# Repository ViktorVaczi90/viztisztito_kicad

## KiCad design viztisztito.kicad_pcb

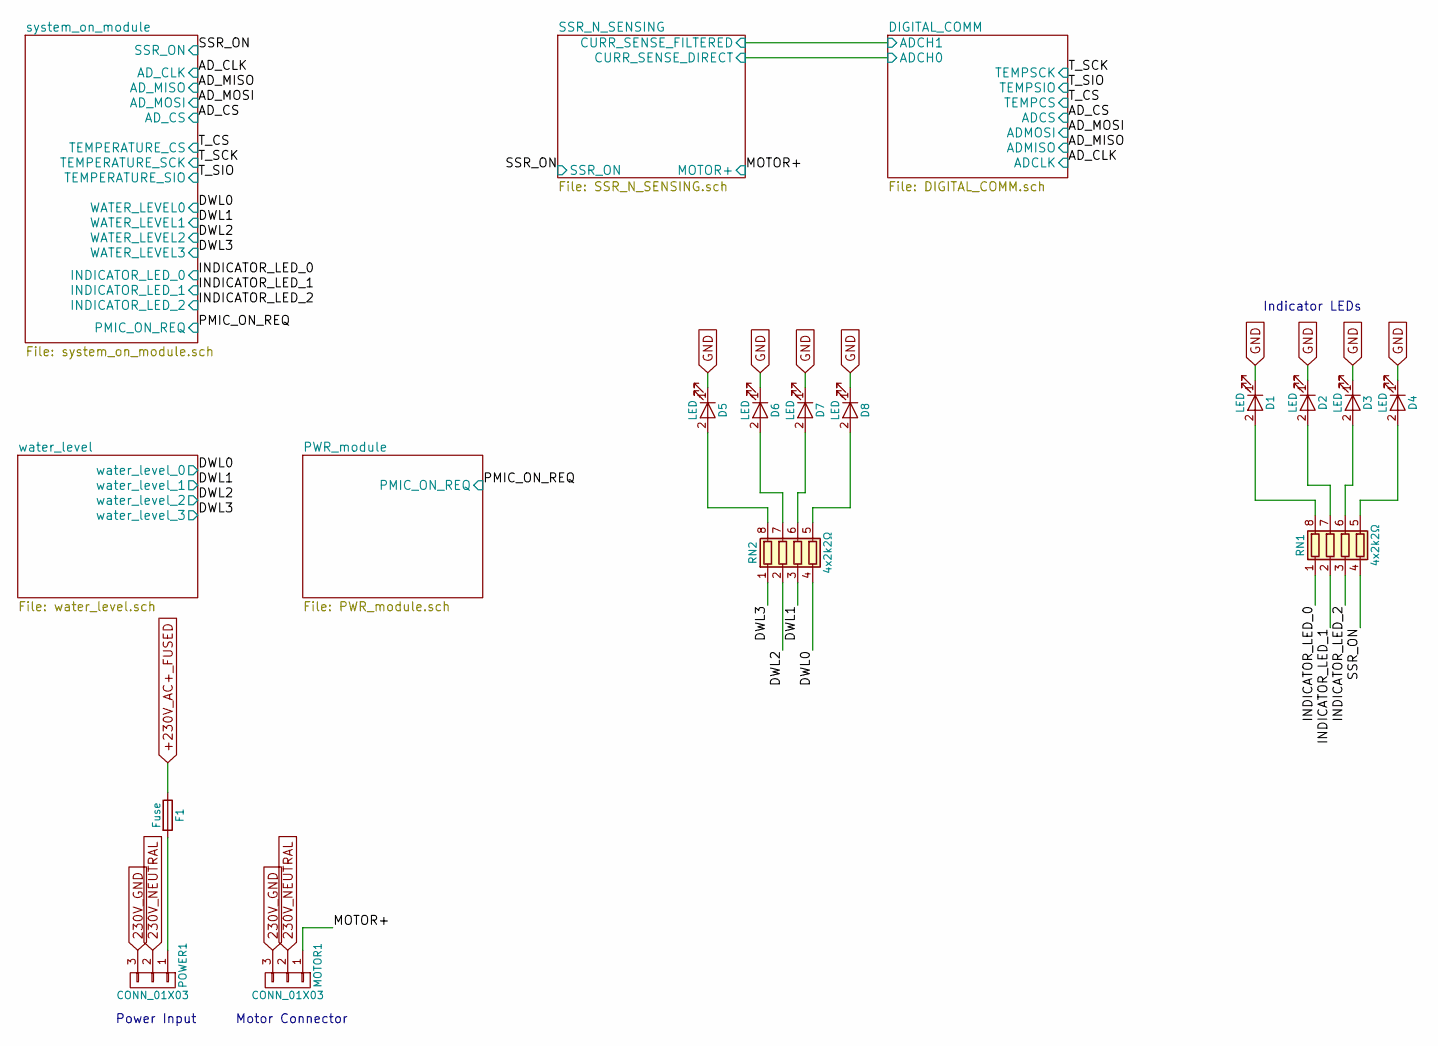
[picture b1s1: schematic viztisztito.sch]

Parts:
D1, D2, D3, D4, D5, D6, D7, D8: LED; LED_1206
F1: Fuse; FUSE-0031.8201
MOTOR1: CONN_01X03; 3x1_TerminalBlock_WAGO-804_RM5mm_3pol
POWER1: CONN_01X03; 3x1_TerminalBlock_WAGO-804_RM5mm_3pol
RN1, RN2: 4x2k2Ω; YC164-Yageo-Handsoldering

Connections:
230V_GND: MOTOR1.3, POWER1.3; also elsewhere on the board
230V_NEUTRAL: MOTOR1.2, POWER1.2; also elsewhere on the board
+230V_AC+_FUSED: F1.1; also elsewhere on the board
/DWL0: RN2.4 (R4.1); also elsewhere on the board
/DWL1: RN2.3 (R3.1); also elsewhere on the board
/DWL2: RN2.2 (R2.1); also elsewhere on the board
/DWL3: RN2.1 (R1.1); also elsewhere on the board
/INDICATOR_LED_0: RN1.1 (R1.1); also elsewhere on the board
/INDICATOR_LED_1: RN1.2 (R2.1); also elsewhere on the board
/INDICATOR_LED_2: RN1.3 (R3.1); also elsewhere on the board
/MOTOR+: MOTOR1.1; also elsewhere on the board
/SSR_ON: RN1.4 (R4.1); also elsewhere on the board
GND: D1.1 (K), D2.1 (K), D3.1 (K), D4.1 (K), D5.1 (K), D6.1 (K), D7.1 (K), D8.1 (K); also elsewhere on the board
unnamed: D1.2 (A), RN1.8 (R1.2)
unnamed: D2.2 (A), RN1.7 (R2.2)
unnamed: D3.2 (A), RN1.6 (R3.2)
unnamed: D4.2 (A), RN1.5 (R4.2)
unnamed: D5.2 (A), RN2.8 (R1.2)
unnamed: D6.2 (A), RN2.7 (R2.2)
unnamed: D7.2 (A), RN2.6 (R3.2)
unnamed: D8.2 (A), RN2.5 (R4.2)
unnamed: F1.2, POWER1.1

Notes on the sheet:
Power Input
Motor Connector
Indicator LEDs

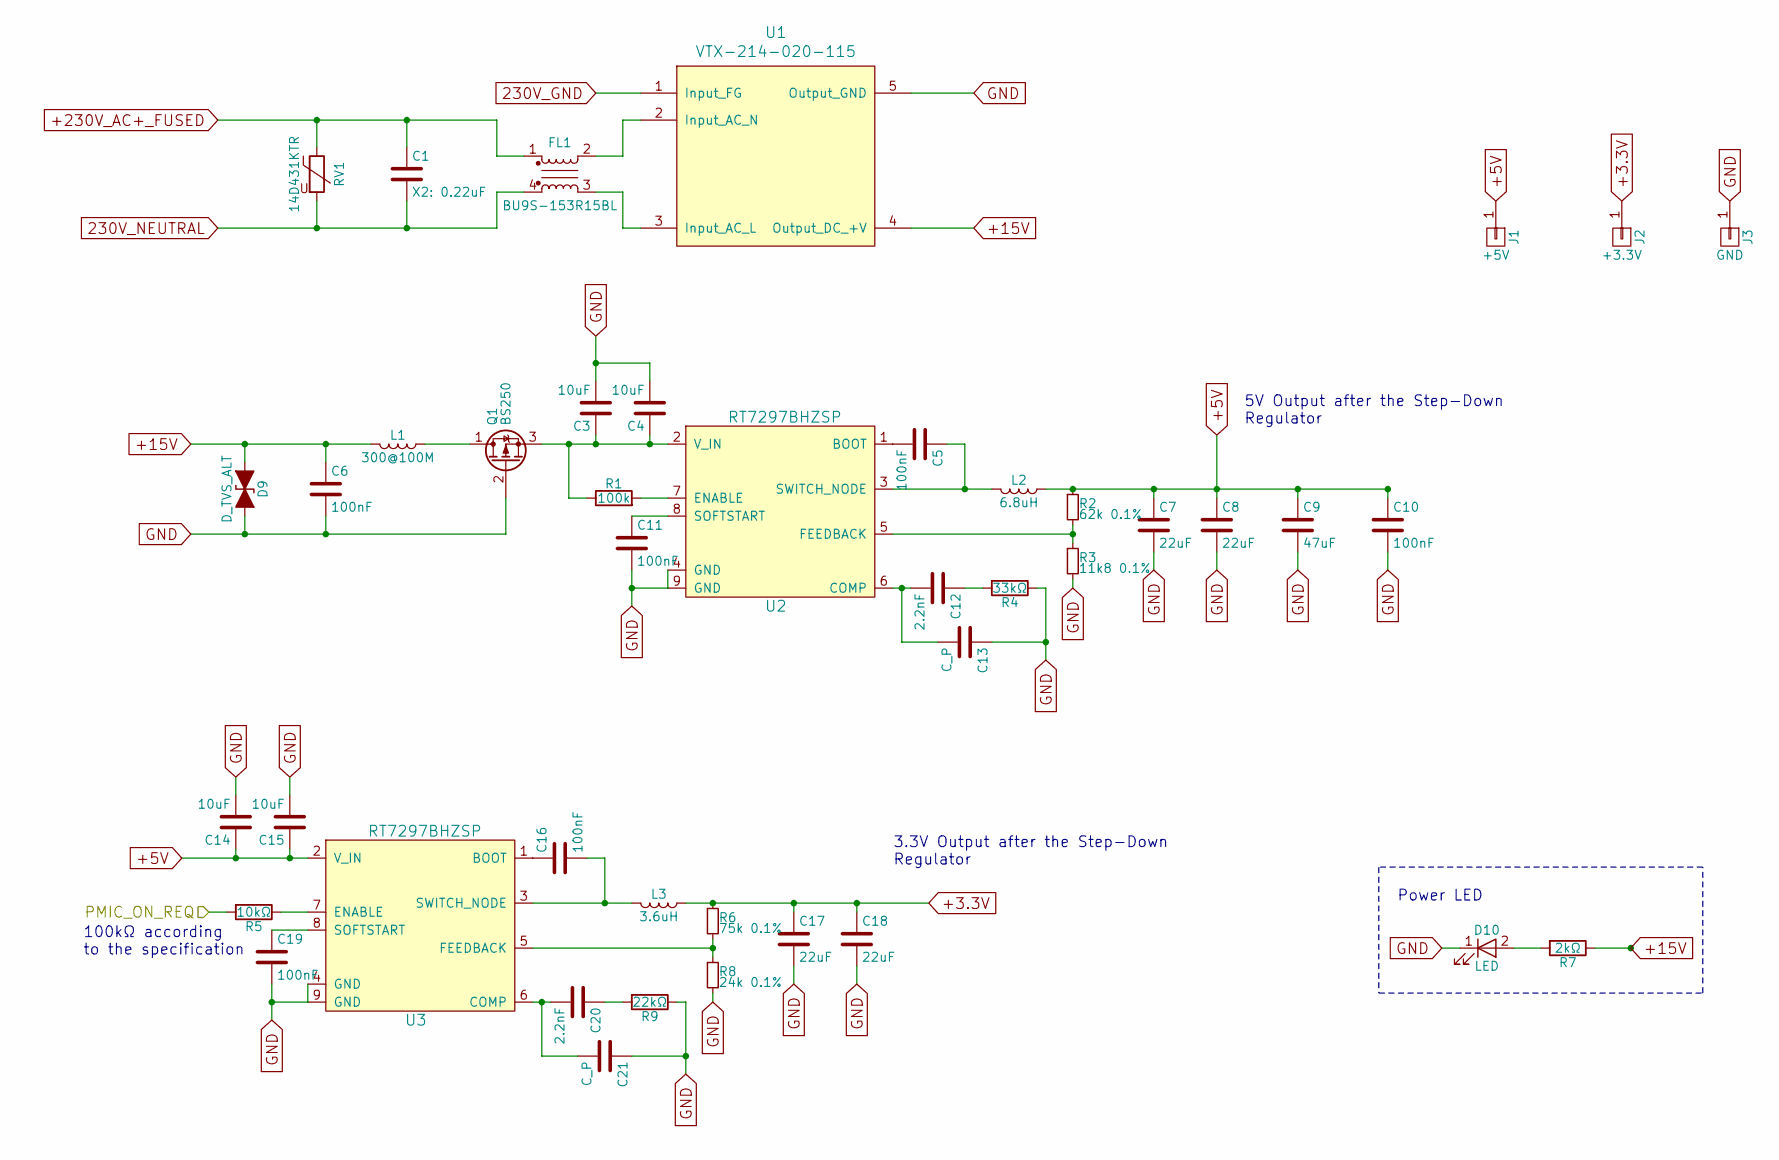
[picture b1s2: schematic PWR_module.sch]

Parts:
C1: X2: 0.22uF; C_Rect_L18.0mm_W8.0mm_P15.00mm_FKS3_FKP3
C3, C4, C14, C15: 10uF; C_0603_HandSoldering
C5, C6, C10, C11, C16, C19: 100nF; C_0603_HandSoldering
C7, C8, C17, C18: 22uF; C_0603_HandSoldering
C9: 47uF; C_1206_HandSoldering
C12, C20: 2.2nF; R_0603_HandSoldering
C13: C_P; C_0603_HandSoldering
C21: C_P; R_0603_HandSoldering
D9: D_TVS_ALT; P6SMB18CA
D10: LED; LED_1206
FL1: BU9S-153R15BL
J1: +5V; PINTST
J2: +3.3V; PINTST
J3: GND; PINTST
L1: 300@100M; L_0603_HandSoldering
L2: 6.8uH; inductors_farnell_2434046_srp1238a-6r8m
L3: 3.6uH; SM-INDUCTOR_12.5mmX12.5mm
Q1: BS250; SOT23
R1: 100k; R_0603_HandSoldering
R2: 62k 0.1%; R_0603_HandSoldering
R3: 11k8 0.1%; R_0603_HandSoldering
R4: 33kΩ; R_0603_HandSoldering
R5: 10kΩ; R_0603_HandSoldering
R6: 75k 0.1%; R_0603_HandSoldering
R7: 2kΩ; R_0603_HandSoldering
R8: 24k 0.1%; R_0603_HandSoldering
R9: 22kΩ; R_0603_HandSoldering
RV1: 14D431KTR; RV_Disc_D21.5_W5.3_P10
U1: VTX-214-020-115
U2, U3: RT7297BHZSP; SOP8_ep_9GND

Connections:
230V_GND: U1.1 (Input_FG); also elsewhere on the board
230V_NEUTRAL: C1.2, FL1.4, RV1.2; also elsewhere on the board
+3.3V: C17.1, C18.1, J2.1, L3.1, R6.1; also elsewhere on the board
+5V: C7.1, C8.1, C9.1, C10.1, C14.1, C15.1, J1.1, L2.1, R2.1, U3.2 (V_IN); also elsewhere on the board
+15V: C6.1, D9.1 (A1), L1.2, R7.1, U1.4 (Output_DC_+V); also elsewhere on the board
+230V_AC+_FUSED: C1.1, FL1.1, RV1.1; also elsewhere on the board
/PMIC_ON_REQ: R5.2; also elsewhere on the board
GND: C3.2, C4.2, C6.2, C7.2, C8.2, C9.2, C10.2, C11.2, C13.1, C14.2, C15.2, C17.2, C18.2, C19.2, C21.1, D9.2 (A2), D10.1 (K), J3.1, Q1.2 (G), R3.2, R4.1, R8.2, R9.1, U1.5 (Output_GND), U2.4 (GND), U2.9 (GND), U3.4 (GND), U3.9 (GND); also elsewhere on the board
unnamed: C3.1, C4.1, Q1.3 (S), R1.1, U2.2 (V_IN)
unnamed: C5.1, L2.2, U2.3 (SWITCH_NODE)
unnamed: C5.2, U2.1 (BOOT)
unnamed: C11.1, U2.8 (SOFTSTART)
unnamed: C12.1, R4.2
unnamed: C12.2, C13.2, U2.6 (COMP)
unnamed: C16.1, U3.1 (BOOT)
unnamed: C16.2, L3.2, U3.3 (SWITCH_NODE)
unnamed: C19.1, U3.8 (SOFTSTART)
unnamed: C20.1, R9.2
unnamed: C20.2, C21.2, U3.6 (COMP)
unnamed: D10.2 (A), R7.2
unnamed: FL1.2, U1.2 (Input_AC_N)
unnamed: FL1.3, U1.3 (Input_AC_L)
unnamed: L1.1, Q1.1 (D)
unnamed: R1.2, U2.7 (ENABLE)
unnamed: R2.2, R3.1, U2.5 (FEEDBACK)
unnamed: R5.1, U3.7 (ENABLE)
unnamed: R6.2, R8.1, U3.5 (FEEDBACK)

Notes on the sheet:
Power LED
5V Output after the Step-Down Regulator
3.3V Output after the Step-Down Regulator
100kΩ according to the specification

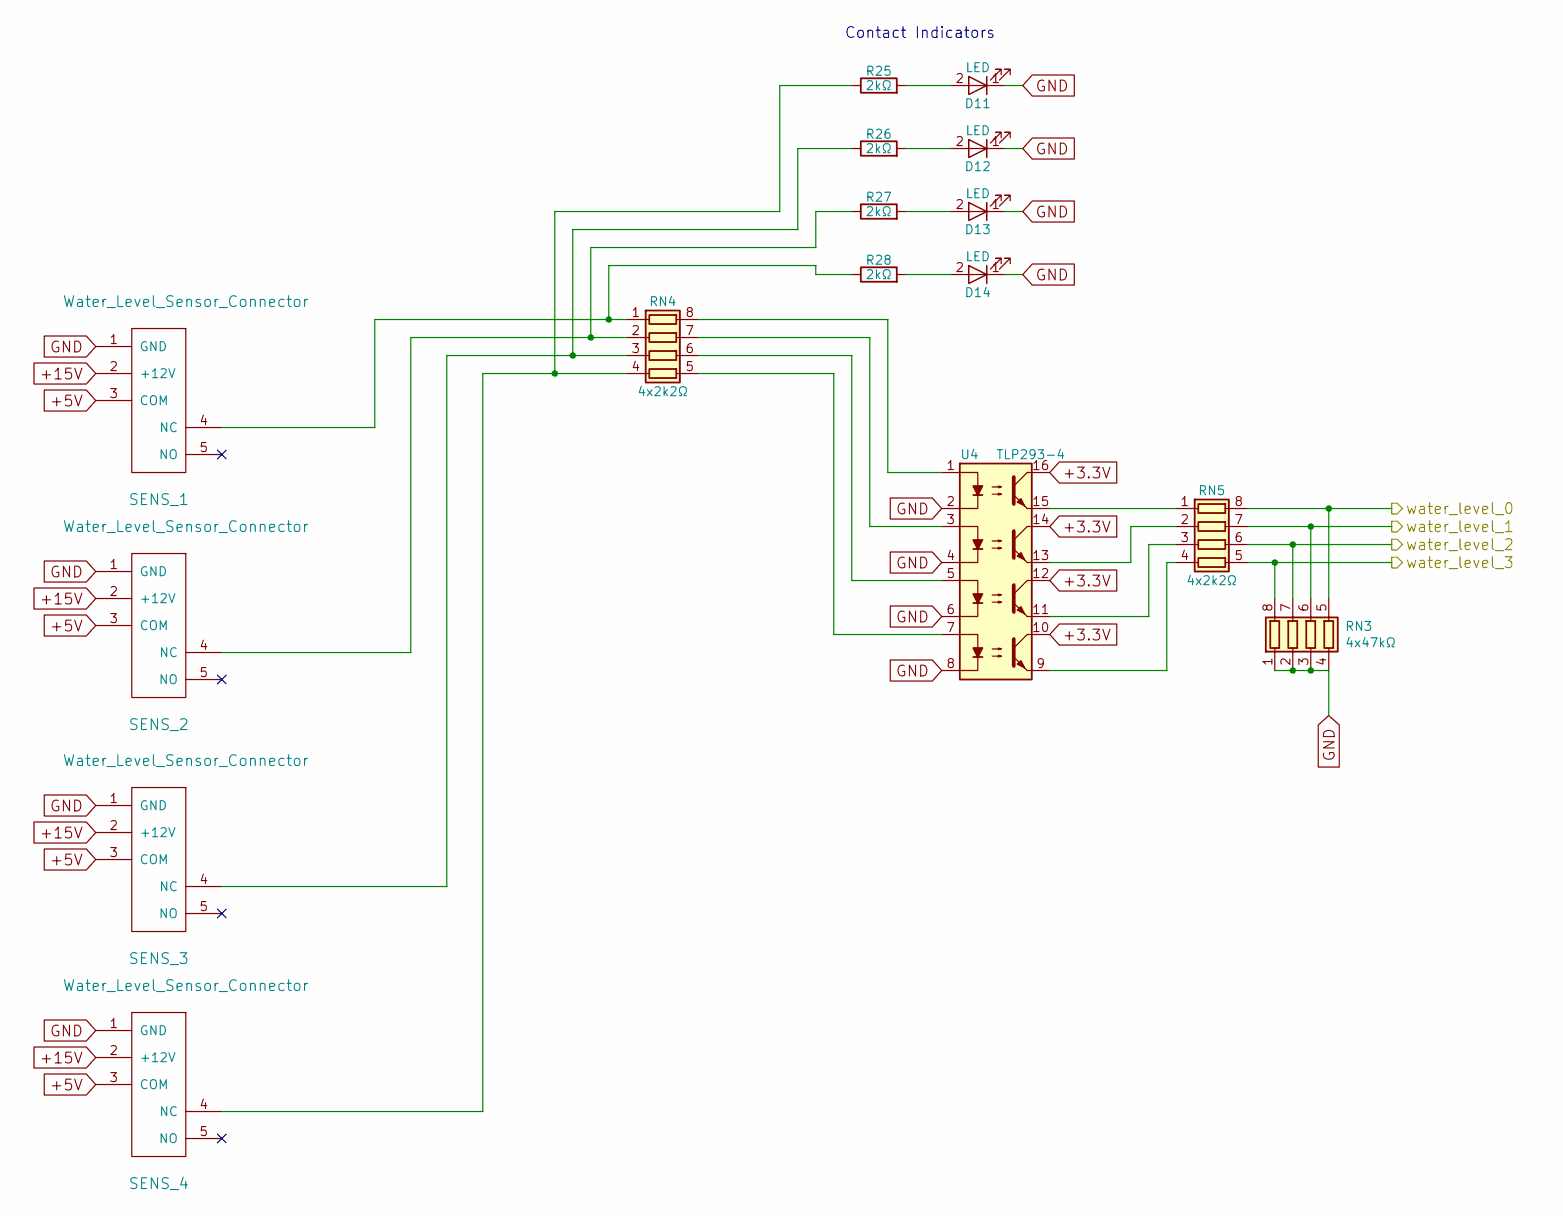
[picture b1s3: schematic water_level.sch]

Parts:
D11, D12, D13, D14: LED; LED_1206
R25, R26, R27, R28: 2kΩ; R_0603_HandSoldering
RN3: 4x47kΩ; YC164-Yageo-Handsoldering
RN4, RN5: 4x2k2Ω; YC164-Yageo-Handsoldering
SENS_1, SENS_2, SENS_3, SENS_4: Water_Level_Sensor_Connector; 5x2_TerminalBlock_WAGO-2604-1105
U4: TLP293-4; DIP-16_W7.62mm_SMDSocket_SmallPads

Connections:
+3.3V: U4.10, U4.12, U4.14, U4.16; also elsewhere on the board
+5V: SENS_1.3 (COM), SENS_2.3 (COM), SENS_3.3 (COM), SENS_4.3 (COM); also elsewhere on the board
+15V: SENS_1.2 (+12V), SENS_2.2 (+12V), SENS_3.2 (+12V), SENS_4.2 (+12V); also elsewhere on the board
/DWL0: RN3.5 (R4.2), RN5.8 (R1.2); also elsewhere on the board
/DWL1: RN3.6 (R3.2), RN5.7 (R2.2); also elsewhere on the board
/DWL2: RN3.7 (R2.2), RN5.6 (R3.2); also elsewhere on the board
/DWL3: RN3.8 (R1.2), RN5.5 (R4.2); also elsewhere on the board
GND: D11.1 (K), D12.1 (K), D13.1 (K), D14.1 (K), RN3.1 (R1.1), RN3.2 (R2.1), RN3.3 (R3.1), RN3.4 (R4.1), SENS_1.1 (GND), SENS_2.1 (GND), SENS_3.1 (GND), SENS_4.1 (GND), U4.2, U4.4, U4.6, U4.8; also elsewhere on the board
unnamed: D11.2 (A), R25.2
unnamed: D12.2 (A), R26.2
unnamed: D13.2 (A), R27.2
unnamed: D14.2 (A), R28.2
unnamed: R25.1, RN4.4 (R4.1), SENS_4.4 (NC)
unnamed: R26.1, RN4.3 (R3.1), SENS_3.4 (NC)
unnamed: R27.1, RN4.2 (R2.1), SENS_2.4 (NC)
unnamed: R28.1, RN4.1 (R1.1), SENS_1.4 (NC)
unnamed: RN4.5 (R4.2), U4.7
unnamed: RN4.6 (R3.2), U4.5
unnamed: RN4.7 (R2.2), U4.3
unnamed: RN4.8 (R1.2), U4.1
unnamed: RN5.1 (R1.1), U4.15
unnamed: RN5.2 (R2.1), U4.13
unnamed: RN5.3 (R3.1), U4.11
unnamed: RN5.4 (R4.1), U4.9

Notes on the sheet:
Contact Indicators

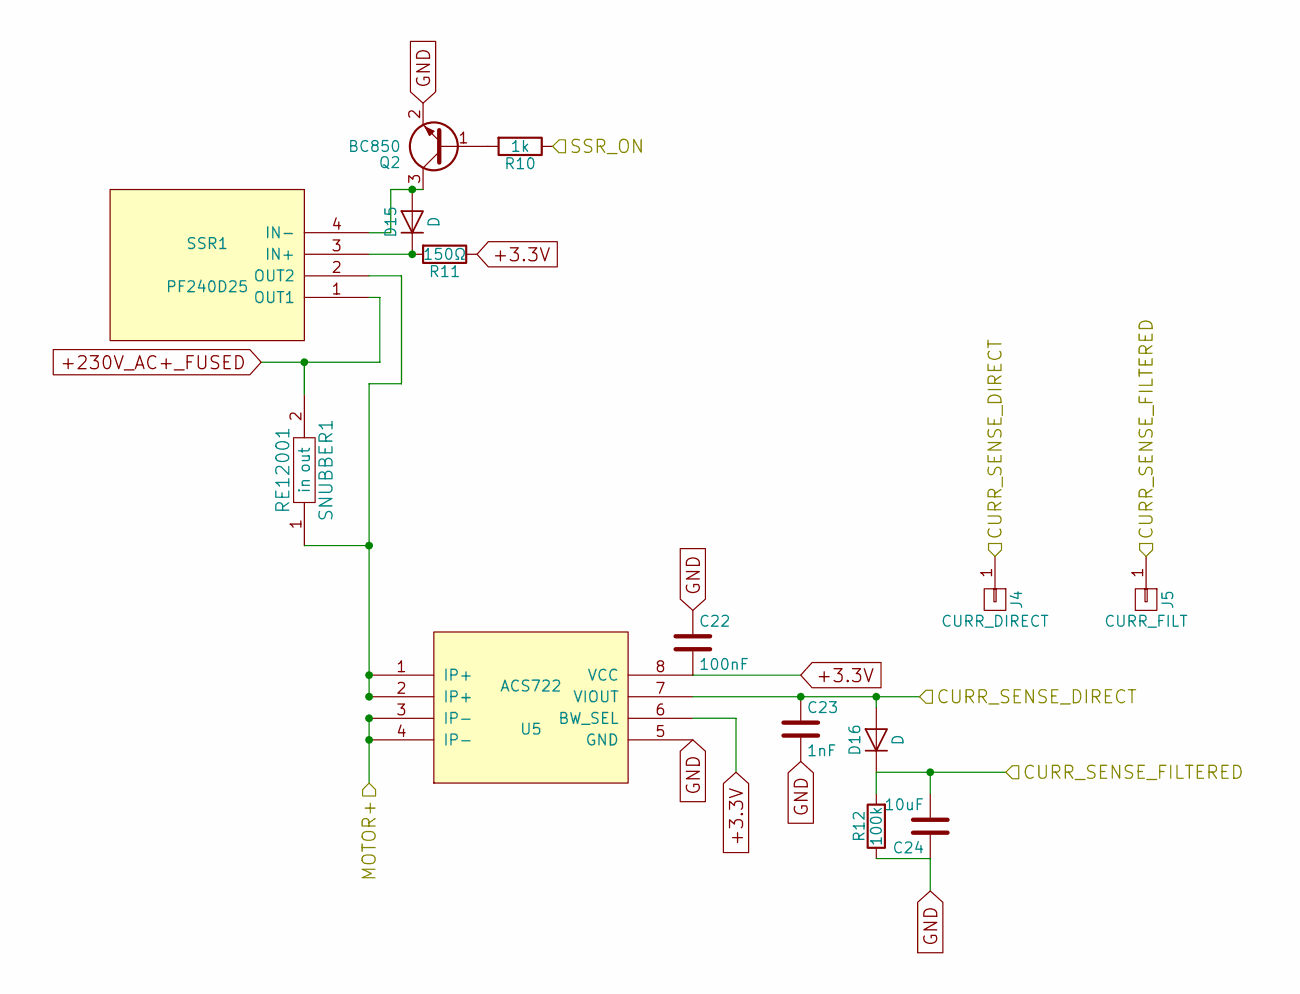
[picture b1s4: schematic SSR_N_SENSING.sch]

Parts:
C22: 100nF; C_0603_HandSoldering
C23: 1nF; C_0603_HandSoldering
C24: 10uF; C_0603_HandSoldering
D15, D16: D; D_SOD-123
J4: CURR_DIRECT; PINTST
J5: CURR_FILT; PINTST
Q2: BC850; SOT-23
R10: 1k; R_0603_HandSoldering
R11: 150Ω; R_0603_HandSoldering
R12: 100k; R_0603_HandSoldering
SNUBBER1: RE12001
SSR1: PF240D25; s202s02
U5: ACS722; SOIC-8_3.9x4.9mm_Pitch1.27mm

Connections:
+3.3V: C22.2, R11.1, U5.6 (BW_SEL), U5.8 (VCC); also elsewhere on the board
+230V_AC+_FUSED: SNUBBER1.2 (out), SSR1.1 (OUT1); also elsewhere on the board
/DIGITAL_COMM/ADCH0: C23.1, D16.2 (A), J4.1, U5.7 (VIOUT); also elsewhere on the board
/DIGITAL_COMM/ADCH1: C24.2, D16.1 (K), J5.1, R12.2; also elsewhere on the board
/MOTOR+: U5.3 (IP-), U5.4 (IP-); also elsewhere on the board
/SSR_ON: R10.1; also elsewhere on the board
GND: C22.1, C23.2, C24.1, Q2.2 (E), R12.1, U5.5 (GND); also elsewhere on the board
unnamed: D15.1 (K), R11.2, SSR1.3 (IN+)
unnamed: D15.2 (A), Q2.3 (C), SSR1.4 (IN-)
unnamed: Q2.1 (B), R10.2
unnamed: SNUBBER1.1 (in), SSR1.2 (OUT2), U5.1 (IP+), U5.2 (IP+)

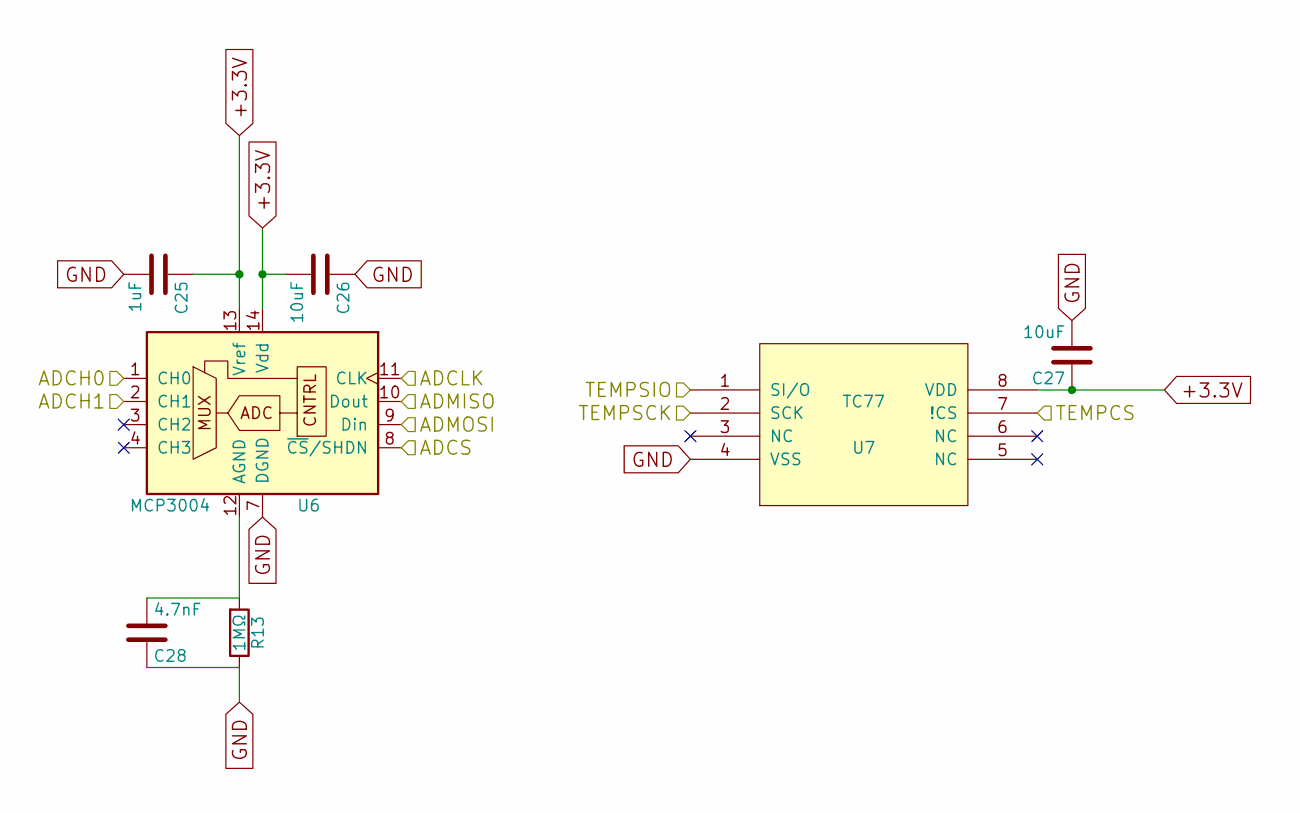
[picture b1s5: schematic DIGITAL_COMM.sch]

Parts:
C25: 1uF; C_0603_HandSoldering
C26, C27: 10uF; C_0603_HandSoldering
C28: 4.7nF; C_0603_HandSoldering
R13: 1MΩ; R_0603_HandSoldering
U6: MCP3004; SOIC-14_3.9x8.7mm_Pitch1.27mm
U7: TC77; SOIC-8_3.9x4.9mm_Pitch1.27mm

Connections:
+3.3V: C25.1, C26.2, C27.1, U6.13 (Vref), U6.14 (Vdd), U7.8 (VDD); also elsewhere on the board
/AD_CLK: U6.11 (CLK); also elsewhere on the board
/AD_CS: U6.8 (~CS~/SHDN); also elsewhere on the board
/AD_MISO: U6.10 (Dout); also elsewhere on the board
/AD_MOSI: U6.9 (Din); also elsewhere on the board
/DIGITAL_COMM/ADCH0: U6.1 (CH0); also elsewhere on the board
/DIGITAL_COMM/ADCH1: U6.2 (CH1); also elsewhere on the board
/T_CS: U7.7 (!CS); also elsewhere on the board
/T_SCK: U7.2 (SCK); also elsewhere on the board
/T_SIO: U7.1 (SI/O); also elsewhere on the board
GND: C25.2, C26.1, C27.2, C28.1, R13.1, U6.7 (DGND), U7.4 (VSS); also elsewhere on the board
unnamed: C28.2, R13.2, U6.12 (AGND)

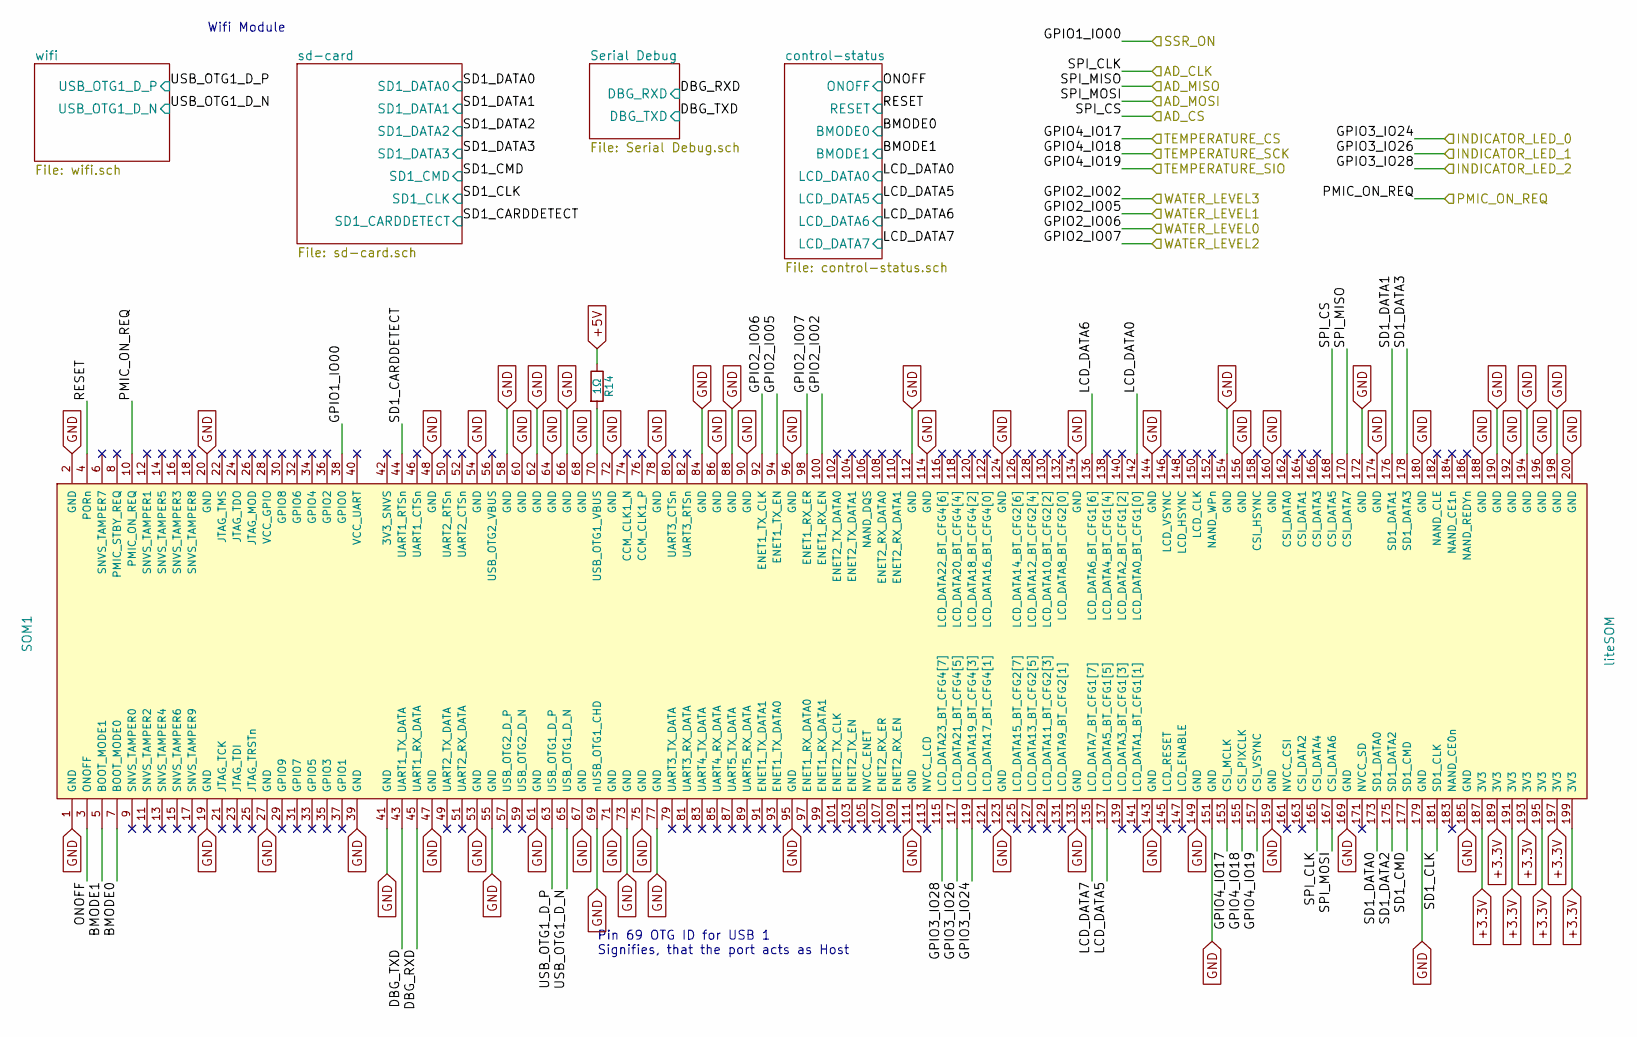
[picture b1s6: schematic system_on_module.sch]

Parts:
R14: 1Ω; R_0603_HandSoldering
SOM1: liteSOM; Socket_SODIMM_DDR1-Farnell_2396418_Debug

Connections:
+3.3V: SOM1.187 (3V3), SOM1.189 (3V3), SOM1.191 (3V3), SOM1.193 (3V3), SOM1.195 (3V3), SOM1.197 (3V3), SOM1.199 (3V3); also elsewhere on the board
+5V: R14.1; also elsewhere on the board
/AD_CLK: SOM1.165 (CSI_DATA4); also elsewhere on the board
/AD_CS: SOM1.168 (CSI_DATA5); also elsewhere on the board
/AD_MISO: SOM1.170 (CSI_DATA7); also elsewhere on the board
/AD_MOSI: SOM1.167 (CSI_DATA6); also elsewhere on the board
/DWL0: SOM1.92 (ENET1_TX_CLK); also elsewhere on the board
/DWL1: SOM1.94 (ENET1_TX_EN); also elsewhere on the board
/DWL2: SOM1.98 (ENET1_RX_ER); also elsewhere on the board
/DWL3: SOM1.100 (ENET1_RX_EN); also elsewhere on the board
/INDICATOR_LED_0: SOM1.119 (LCD_DATA19_BT_CFG4[3]); also elsewhere on the board
/INDICATOR_LED_1: SOM1.117 (LCD_DATA21_BT_CFG4[5]); also elsewhere on the board
/INDICATOR_LED_2: SOM1.115 (LCD_DATA23_BT_CFG4[7]); also elsewhere on the board
/PMIC_ON_REQ: SOM1.10 (PMIC_ON_REQ); also elsewhere on the board
/SSR_ON: SOM1.38 (GPIO0); also elsewhere on the board
/T_CS: SOM1.153 (CSI_MCLK); also elsewhere on the board
/T_SCK: SOM1.155 (CSI_PIXCLK); also elsewhere on the board
/T_SIO: SOM1.157 (CSI_VSYNC); also elsewhere on the board
/system_on_module/BMODE0: SOM1.7 (BOOT_MODE0); also elsewhere on the board
/system_on_module/BMODE1: SOM1.5 (BOOT_MODE1); also elsewhere on the board
/system_on_module/DBG_RXD: SOM1.45 (UART1_RX_DATA); also elsewhere on the board
/system_on_module/DBG_TXD: SOM1.43 (UART1_TX_DATA); also elsewhere on the board
/system_on_module/LCD_DATA0: SOM1.142 (LCD_DATA0_BT_CFG1[0]); also elsewhere on the board
/system_on_module/LCD_DATA5: SOM1.137 (LCD_DATA5_BT_CFG1[5]); also elsewhere on the board
/system_on_module/LCD_DATA6: SOM1.136 (LCD_DATA6_BT_CFG1[6]); also elsewhere on the board
/system_on_module/LCD_DATA7: SOM1.135 (LCD_DATA7_BT_CFG1[7]); also elsewhere on the board
/system_on_module/ONOFF: SOM1.3 (ONOFF); also elsewhere on the board
/system_on_module/RESET: SOM1.4 (PORn); also elsewhere on the board
/system_on_module/SD1_CARDDETECT: SOM1.44 (UART1_RTSn); also elsewhere on the board
/system_on_module/SD1_CLK: SOM1.181 (SD1_CLK); also elsewhere on the board
/system_on_module/SD1_CMD: SOM1.177 (SD1_CMD); also elsewhere on the board
/system_on_module/SD1_DATA0: SOM1.173 (SD1_DATA0); also elsewhere on the board
/system_on_module/SD1_DATA1: SOM1.176 (SD1_DATA1); also elsewhere on the board
/system_on_module/SD1_DATA2: SOM1.175 (SD1_DATA2); also elsewhere on the board
/system_on_module/SD1_DATA3: SOM1.178 (SD1_DATA3); also elsewhere on the board
/system_on_module/USB_OTG1_D_N: SOM1.65 (USB_OTG1_D_N); also elsewhere on the board
/system_on_module/USB_OTG1_D_P: SOM1.63 (USB_OTG1_D_P); also elsewhere on the board
GND: SOM1.1 (GND), SOM1.2 (GND), SOM1.19 (GND), SOM1.20 (GND), SOM1.27 (GND), SOM1.39 (GND), SOM1.41 (GND), SOM1.47 (GND), SOM1.48 (GND), SOM1.53 (GND), SOM1.54 (GND), SOM1.55 (GND), SOM1.58 (GND), SOM1.60 (GND), SOM1.61 (GND), SOM1.62 (GND), SOM1.64 (GND), SOM1.66 (GND), SOM1.67 (GND), SOM1.68 (GND), SOM1.69 (nUSB_OTG1_CHD), SOM1.71 (GND), SOM1.72 (GND), SOM1.73 (GND), SOM1.75 (GND), SOM1.77 (GND), SOM1.78 (GND), SOM1.84 (GND), SOM1.86 (GND), SOM1.88 (GND), SOM1.90 (GND), SOM1.95 (GND), SOM1.96 (GND), SOM1.111 (GND), SOM1.112 (GND), SOM1.114 (GND), SOM1.123 (GND), SOM1.124 (GND), SOM1.133 (GND), SOM1.134 (GND), SOM1.143 (GND), SOM1.144 (GND), SOM1.149 (GND), SOM1.151 (GND), SOM1.154 (GND), SOM1.156 (GND), SOM1.159 (GND), SOM1.160 (GND), SOM1.169 (GND), SOM1.172 (GND), SOM1.174 (GND), SOM1.179 (GND), SOM1.180 (GND), SOM1.185 (GND), SOM1.188 (GND), SOM1.190 (GND), SOM1.192 (GND), SOM1.194 (GND), SOM1.196 (GND), SOM1.198 (GND), SOM1.200 (GND); also elsewhere on the board
unnamed: R14.2, SOM1.70 (USB_OTG1_VBUS)

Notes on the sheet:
Wifi Module
Pin 69 OTG ID for USB 1 Signifies, that the port acts as Host

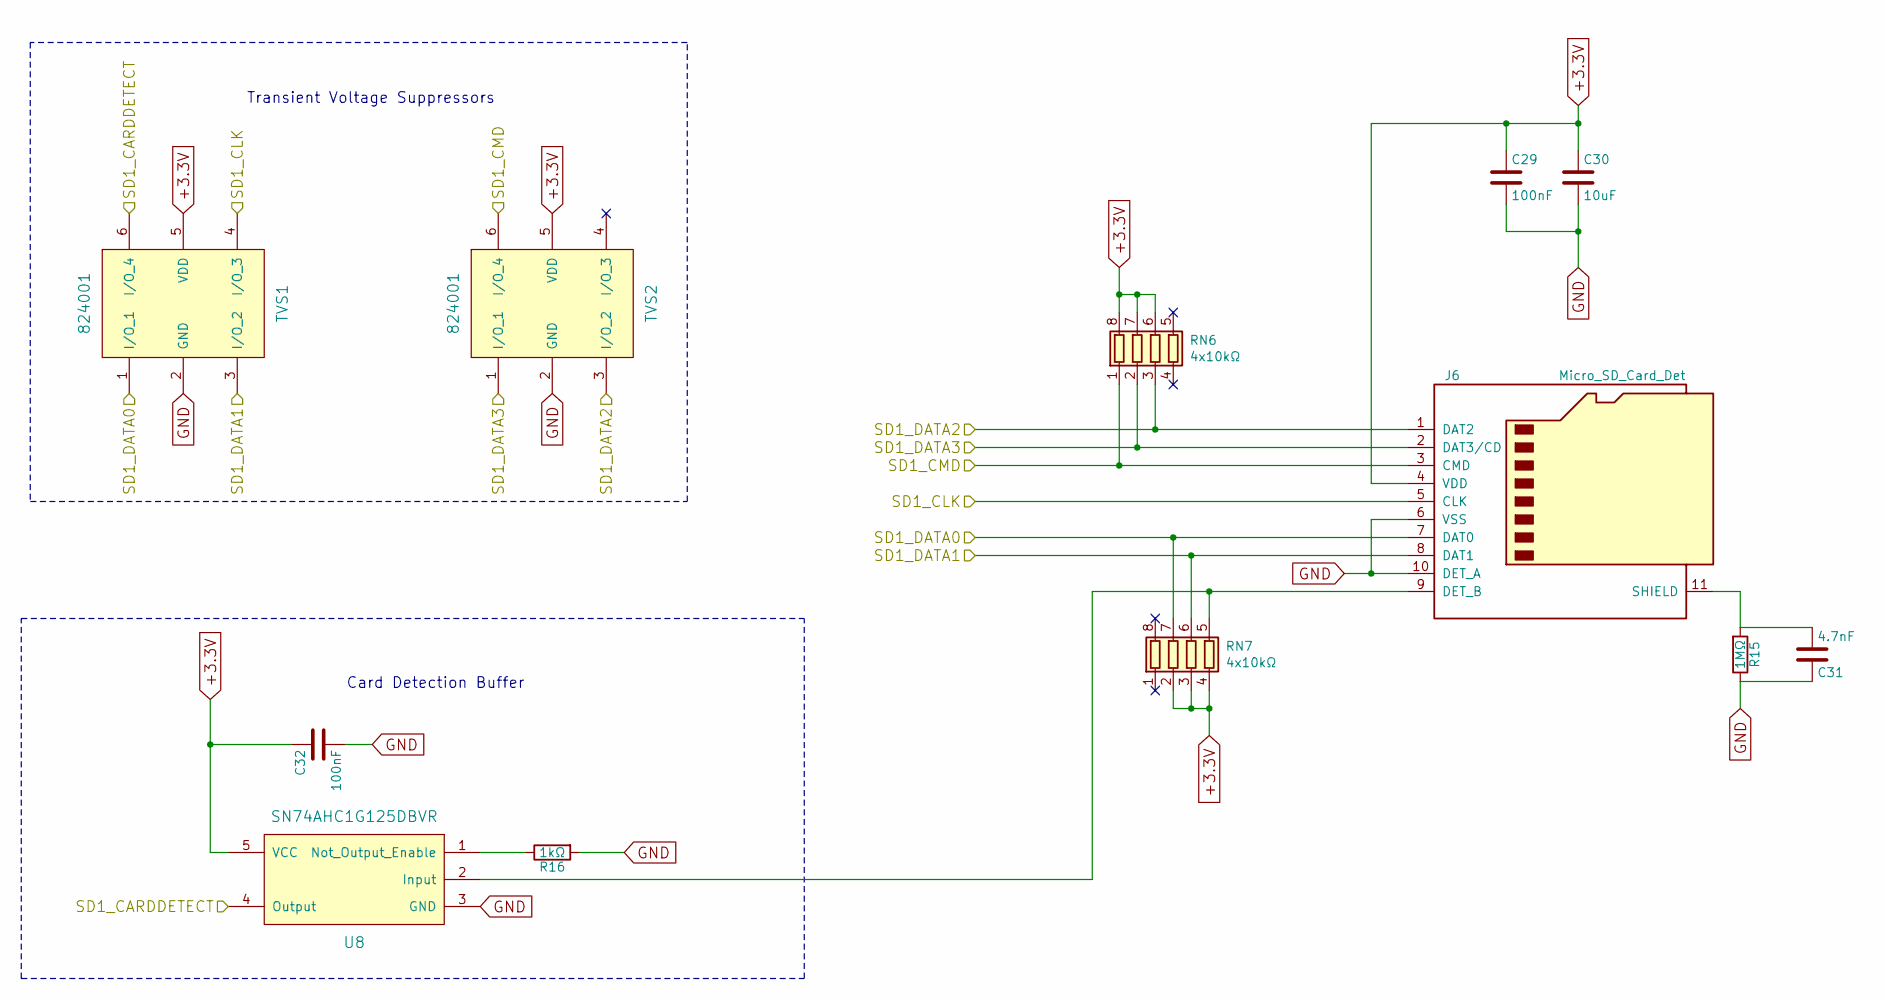
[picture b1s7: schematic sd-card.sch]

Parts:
C29, C32: 100nF; C_0603_HandSoldering
C30: 10uF; C_0603_HandSoldering
C31: 4.7nF; C_0603_HandSoldering
J6: Micro_SD_Card_Det; microSD_Card_Receptacle_Hirose_DM3AT-SF-PEJM5
R15: 1MΩ; R_0603_HandSoldering
R16: 1kΩ; R_0603_HandSoldering
RN6, RN7: 4x10kΩ; YC164-Yageo-Handsoldering
TVS1, TVS2: 824001; SOT-23-6
U8: SN74AHC1G125DBVR; SOT-23-5

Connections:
+3.3V: C29.1, C30.1, C32.1, J6.4 (VDD), RN6.6 (R3.2), RN6.7 (R2.2), RN6.8 (R1.2), RN7.2 (R2.1), RN7.3 (R3.1), RN7.4 (R4.1), TVS1.5 (VDD), TVS2.5 (VDD), U8.5 (VCC); also elsewhere on the board
/system_on_module/SD1_CARDDETECT: TVS1.6 (I/O_4), U8.4 (Output); also elsewhere on the board
/system_on_module/SD1_CLK: J6.5 (CLK), TVS1.4 (I/O_3); also elsewhere on the board
/system_on_module/SD1_CMD: J6.3 (CMD), RN6.1 (R1.1), TVS2.6 (I/O_4); also elsewhere on the board
/system_on_module/SD1_DATA0: J6.7 (DAT0), RN7.7 (R2.2), TVS1.1 (I/O_1); also elsewhere on the board
/system_on_module/SD1_DATA1: J6.8 (DAT1), RN7.6 (R3.2), TVS1.3 (I/O_2); also elsewhere on the board
/system_on_module/SD1_DATA2: J6.1 (DAT2), RN6.3 (R3.1), TVS2.3 (I/O_2); also elsewhere on the board
/system_on_module/SD1_DATA3: J6.2 (DAT3/CD), RN6.2 (R2.1), TVS2.1 (I/O_1); also elsewhere on the board
GND: C29.2, C30.2, C31.1, C32.2, J6.6 (VSS), J6.10 (DET_A), R15.1, R16.2, TVS1.2 (GND), TVS2.2 (GND), U8.3 (GND); also elsewhere on the board
unnamed: C31.2, J6.11 (SHIELD), R15.2
unnamed: J6.9 (DET_B), RN7.5 (R4.2), U8.2 (Input)
unnamed: R16.1, U8.1 (Not_Output_Enable)

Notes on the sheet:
Transient Voltage Suppressors
Card Detection Buffer

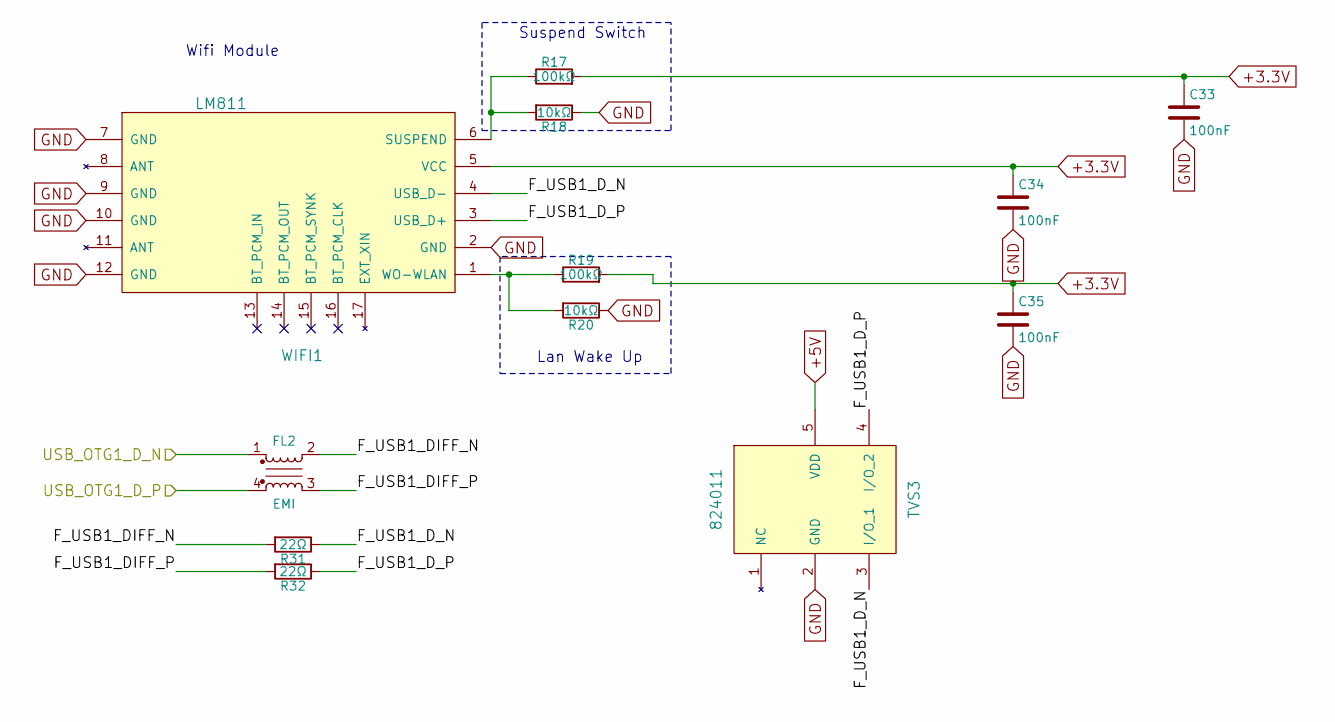
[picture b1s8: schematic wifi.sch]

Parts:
C33, C34, C35: 100nF; C_0603_HandSoldering
FL2: EMI; 744233121
R17, R19: 100kΩ; R_0603_HandSoldering
R18, R20: 10kΩ; R_0603_HandSoldering
R31, R32: 22Ω; R_0603_HandSoldering
TVS3: 824011; SOT-23-5
WIFI1: LM811

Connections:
+3.3V: C33.1, C34.1, C35.1, R17.2, R19.2, WIFI1.5 (VCC); also elsewhere on the board
+5V: TVS3.5 (VDD); also elsewhere on the board
/system_on_module/USB_OTG1_D_N: FL2.1; also elsewhere on the board
/system_on_module/USB_OTG1_D_P: FL2.4; also elsewhere on the board
/system_on_module/wifi/F_USB1_DIFF_N: FL2.2, R31.2
/system_on_module/wifi/F_USB1_DIFF_P: FL2.3, R32.2
/system_on_module/wifi/F_USB1_D_N: R31.1, TVS3.3 (I/O_1), WIFI1.4 (USB_D-)
/system_on_module/wifi/F_USB1_D_P: R32.1, TVS3.4 (I/O_2), WIFI1.3 (USB_D+)
GND: C33.2, C34.2, C35.2, R18.1, R20.1, TVS3.2 (GND), WIFI1.2 (GND), WIFI1.7 (GND), WIFI1.9 (GND), WIFI1.10 (GND), WIFI1.12 (GND); also elsewhere on the board
unnamed: R17.1, R18.2, WIFI1.6 (SUSPEND)
unnamed: R19.1, R20.2, WIFI1.1 (WO-WLAN)

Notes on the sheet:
Wifi Module
Suspend Switch
Lan Wake Up

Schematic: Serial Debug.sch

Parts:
C36, C45: 10uF; C_0603_HandSoldering
C37, C38, C40, C46: 100nF; C_0603_HandSoldering
C39: 4.7nF; C_0603_HandSoldering
C41, C42: 47pF; C_0603_HandSoldering
C43: 10nF; C_0603_HandSoldering
C44: 100uF; CP_Elec_6.3x5.7
D18, D19: LED; LED_1206
FL3: EMI; 744233121
J7: USB_OTG; USB_Micro-B_Vertical_Molex-105133-0001
L4: L; L_0603_HandSoldering
R21: 1MΩ; R_0603_HandSoldering
R22, R23: 22Ω; R_0603_HandSoldering
R29, R30: 2kΩ; R_0603_HandSoldering
TVS4: 824011; SOT-23-5
U9: FT230XQ; QFN-16-1EP_4x4mm_Pitch0.65mm

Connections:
+3.3V: C38.1, C43.1, R29.2, R30.2, U9.1 (VCCIO), U9.9 (RESET#); also elsewhere on the board
/system_on_module/DBG_RXD: U9.15 (TXD); also elsewhere on the board
/system_on_module/DBG_TXD: U9.2 (RXD); also elsewhere on the board
/system_on_module/Serial Debug/5V_USB: C36.2, C37.1, C44.1, C45.2, L4.2, U9.10 (VCC)
/system_on_module/Serial Debug/DBG_USB_D_N: FL3.3, J7.2 (D-), TVS4.4 (I/O_2)
/system_on_module/Serial Debug/DBG_USB_D_P: FL3.2, J7.3 (D+), TVS4.3 (I/O_1)
/system_on_module/Serial Debug/DL+: C41.2, FL3.1, R23.1
/system_on_module/Serial Debug/DL-: C42.2, FL3.4, R22.1
/system_on_module/Serial Debug/SER_USB+: R23.2, U9.6 (USBD+)
/system_on_module/Serial Debug/SER_USB-: R22.2, U9.7 (USBD-)
/system_on_module/Serial Debug/USB1_VCC: C46.1, J7.1 (VBUS), L4.1, TVS4.5 (VDD)
GND: C36.1, C37.2, C38.2, C39.2, C40.1, C41.1, C42.1, C43.2, C44.2, C45.1, C46.2, J7.5 (GND), R21.2, TVS4.2 (GND), U9.3 (GND), U9.13 (GND), U9.17 (GND); also elsewhere on the board
unnamed: C39.1, J7.6 (Shield), R21.1
unnamed: C40.2, U9.8 (3V3OUT)
unnamed: D18.1 (K), U9.11 (CBUS1)
unnamed: D18.2 (A), R29.1
unnamed: D19.1 (K), U9.5 (CBUS2)
unnamed: D19.2 (A), R30.1

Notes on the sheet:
Surge Protection

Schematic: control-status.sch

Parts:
C47: 10nF; C_0603_HandSoldering
C48, C49: 100nF; C_0603_HandSoldering
D17: LED; LED_1206
R24: 2kΩ; R_0603_HandSoldering
RN8, RN10: 4x10kΩ; YC164-Yageo-Handsoldering
RN9, RN11: 4x47kΩ; YC164-Yageo-Handsoldering
S1: SW_DIP_x6; DIP-12_W7.62mm_LongPads
SW1, SW2: SW_PUSH; EVQQ2202W
U10: MAX803; SOT-23

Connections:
+3.3V: C49.1, R24.2, RN8.2 (R2.1), RN8.3 (R3.1), RN8.4 (R4.1), RN10.1 (R1.1), RN10.2 (R2.1), RN10.3 (R3.1), U10.3 (VCC); also elsewhere on the board
/system_on_module/BMODE0: RN9.2 (R2.1), S1.12; also elsewhere on the board
/system_on_module/BMODE1: RN9.3 (R3.1), S1.11; also elsewhere on the board
/system_on_module/LCD_DATA0: RN11.3 (R3.1), S1.7; also elsewhere on the board
/system_on_module/LCD_DATA5: RN11.2 (R2.1), S1.8; also elsewhere on the board
/system_on_module/LCD_DATA6: RN11.1 (R1.1), S1.9; also elsewhere on the board
/system_on_module/LCD_DATA7: RN9.4 (R4.1), S1.10; also elsewhere on the board
/system_on_module/ONOFF: C47.1, SW1.2; also elsewhere on the board
/system_on_module/RESET: C48.1, SW2.1, U10.2 (~RESET); also elsewhere on the board
GND: C47.2, C48.2, C49.2, D17.1 (K), RN9.5 (R4.2), RN9.6 (R3.2), RN9.7 (R2.2), RN11.6 (R3.2), RN11.7 (R2.2), RN11.8 (R1.2), SW1.1, SW2.2, U10.1 (GND); also elsewhere on the board
unnamed: D17.2 (A), R24.1
unnamed: RN8.5 (R4.2), S1.3
unnamed: RN8.6 (R3.2), S1.2
unnamed: RN8.7 (R2.2), S1.1
unnamed: RN10.6 (R3.2), S1.6
unnamed: RN10.7 (R2.2), S1.5
unnamed: RN10.8 (R1.2), S1.4

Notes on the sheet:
Status LED
Power Switch
Reset
Higher Resistance than the other side!
Boot Config
